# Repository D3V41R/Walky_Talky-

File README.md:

**Walky-Talky**

Walky-Talky is a custom **STM32-based** digital voice communication system built for long-range, low-bandwidth voice transmission over LoRa RF.

The project combines embedded firmware development, custom PCB design in KiCad, digital signal processing, and wireless communication into a fully self-contained handheld device.

Voice audio is captured using an INMP441 I2S microphone, compressed in real time using the Codec2 low-bitrate voice codec, and transmitted through a RYLR998 LoRa module operating at 915 MHz. On the receiving side, audio is decoded and played back through a 12-bit DAC and PAM8403 speaker amplifier.

To support continuous real-time streaming, STM32 DMA is used throughout both the audio and RF pipelines, minimizing CPU overhead while maintaining low-latency operation.

The hardware was designed entirely from scratch in KiCad and includes custom analog audio circuitry, rotary encoder channel selection, power regulation, and RF interfacing on a fully custom PCB.

**Features**
-Real-time digital voice communication over LoRa
-Codec2 low-bitrate voice compression
-STM32 DMA-driven audio streaming
-INMP441 I2S microphone input
-12-bit DAC audio playback
-PAM8403 speaker amplifier output
-Rotary encoder channel selection
-Fully custom KiCad PCB design
-Embedded real-time firmware architecture

**System Diagram**

**Hardware Overview**

Schematic:

PCB Renderings: 

**Technologies Used**
STM32
KiCad
LoRa / RYLR998
Codec2
I2S Audio
DMA Streaming
Embedded C
Digital Signal Processing
Custom PCB Design

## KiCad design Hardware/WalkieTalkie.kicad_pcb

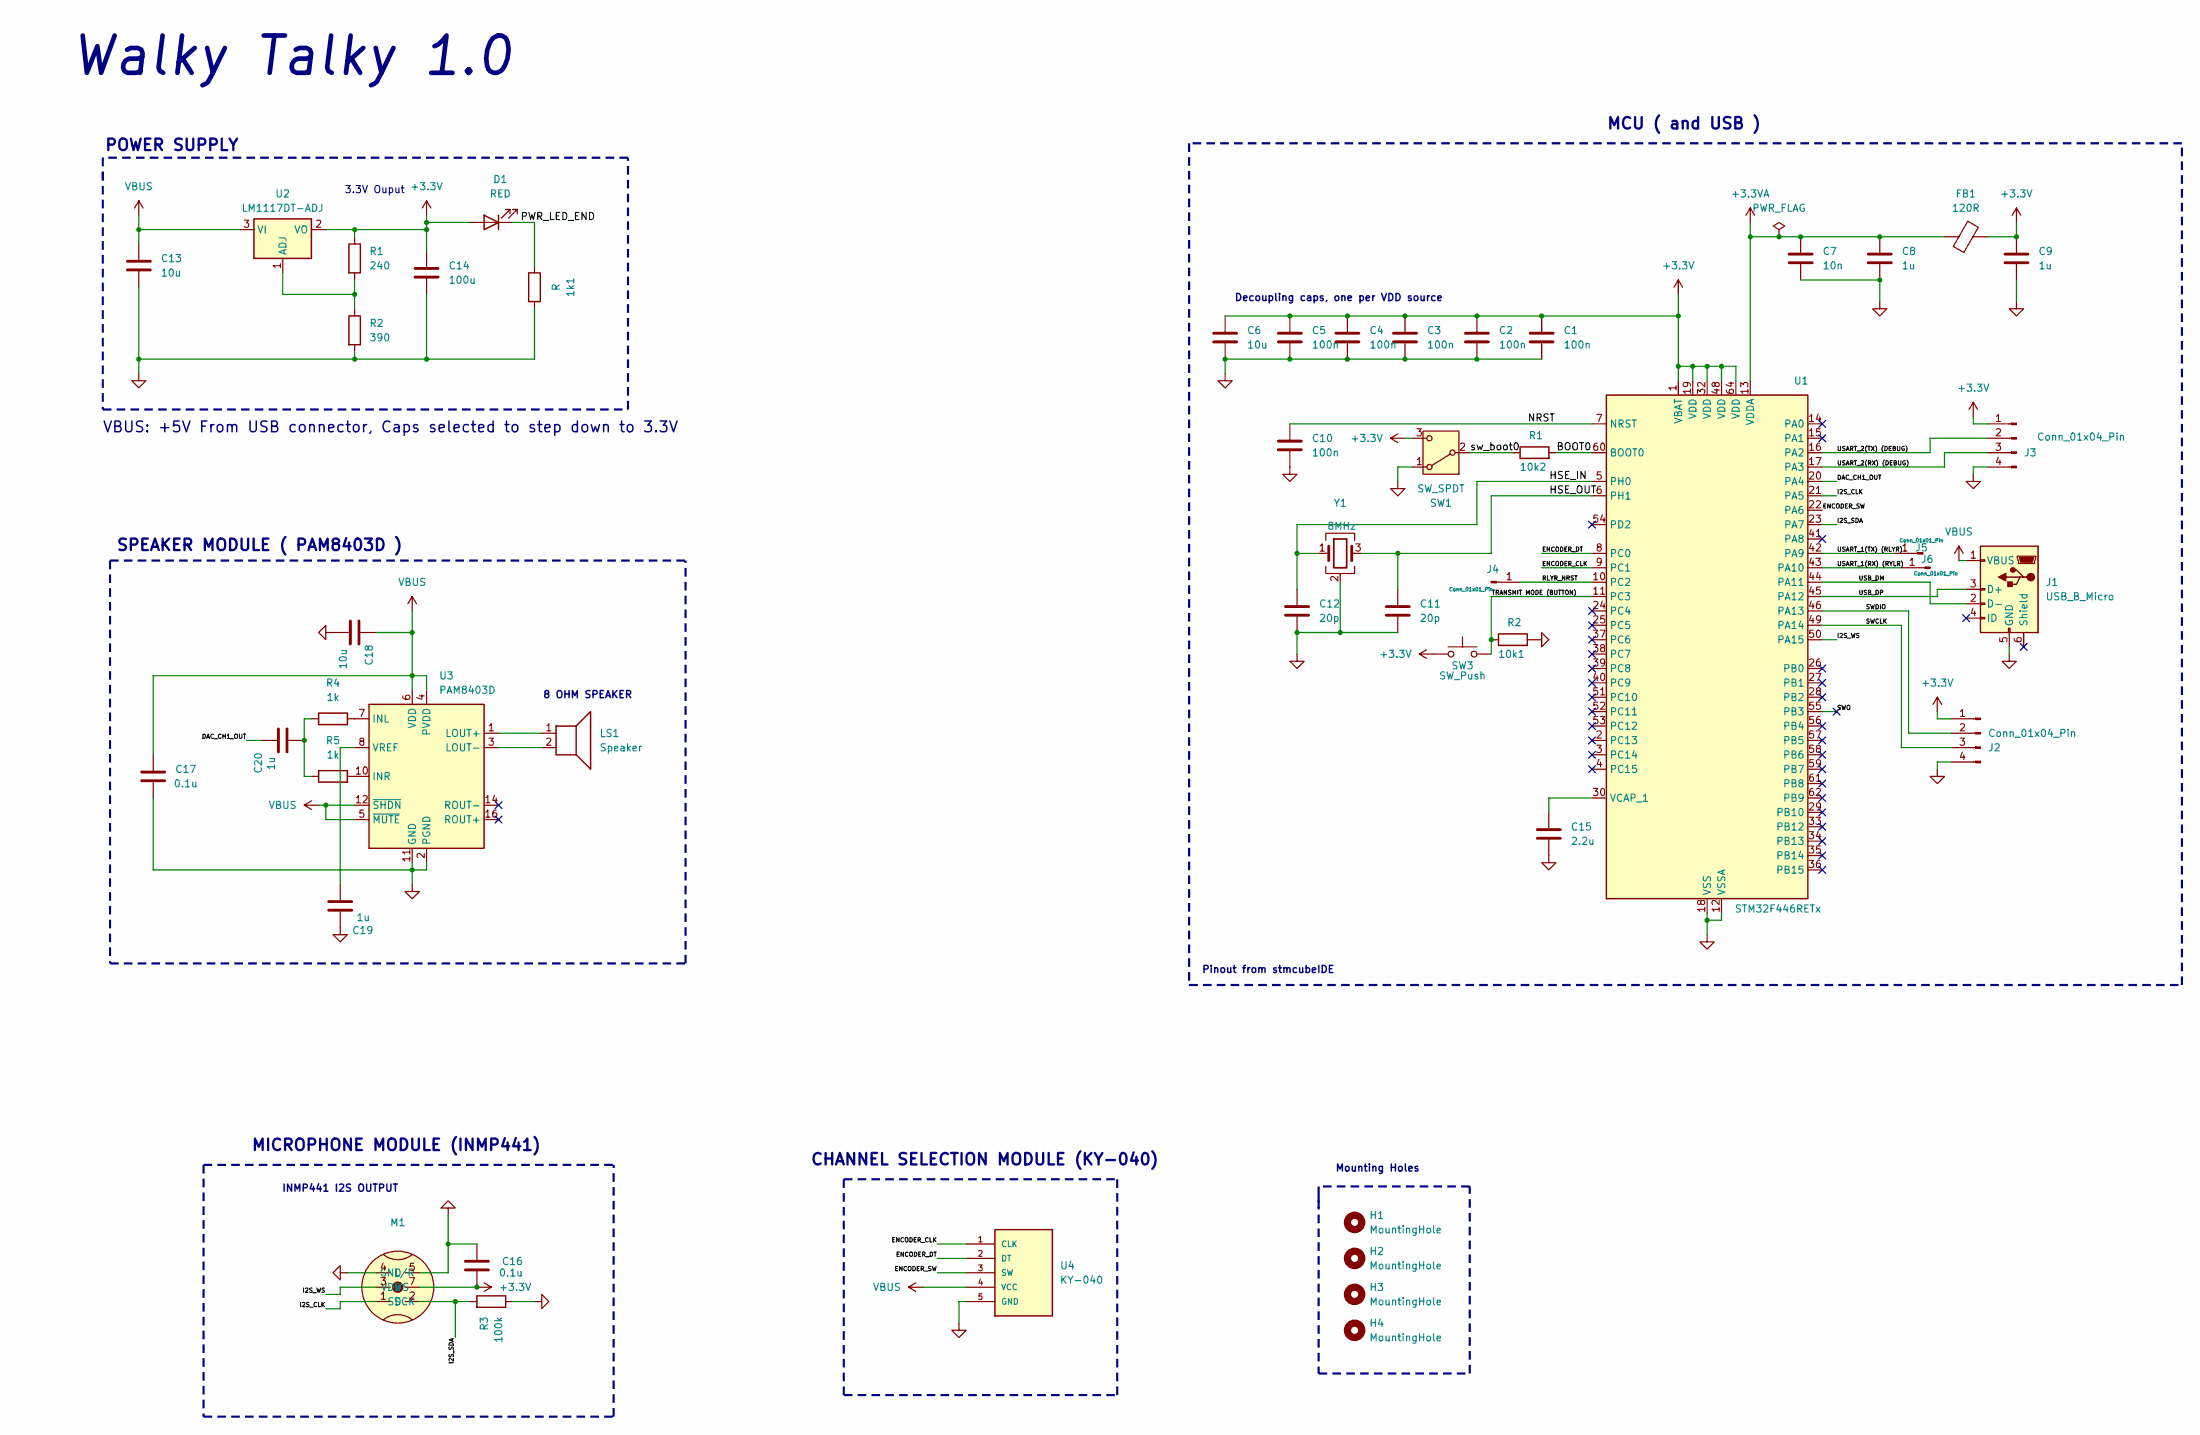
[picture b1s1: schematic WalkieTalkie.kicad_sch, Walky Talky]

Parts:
1k1: R; R_0603_1608Metric
10k1: R2; R_0603_1608Metric
10k2: R1; R_0603_1608Metric
C1, C2, C3, C4, C5, C10: 100n; C_0603_1608Metric
C6, C13, C18: 10u; C_0603_1608Metric
C7: 10n; C_0603_1608Metric
C8, C9, C19, C20: 1u; C_0603_1608Metric
C11, C12: 20p; C_0603_1608Metric
C14: 100u; C_0603_1608Metric
C15: 2.2u; C_0603_1608Metric
C16, C17: 0.1u; C_0603_1608Metric
D1: RED; LED_0201_0603Metric
FB1: 120R; L_0603_1608Metric
H1, H2, H3, H4: MountingHole; MountingHole_2.2mm_M2
J1: USB_B_Micro; USB_Micro-B_Wuerth_629105150521
J2, J3: Conn_01x04_Pin; PinHeader_1x04_P2.54mm_Vertical
J4, J5, J6: Conn_01x01_Pin; PinSocket_1x01_P2.54mm_Horizontal
LS1: Speaker; PinHeader_1x02_P2.54mm_Vertical
M1: MIC_INMP441ACEZ-R7
R1: 240; R_0603_1608Metric
R2: 390; R_0603_1608Metric
R3: 100k; R_0603_1608Metric
R4, R5: 1k; R_0603_1608Metric
SW1: SW_SPDT; SW_SPDT_PCM12
SW3: SW_Push; SW_DIP_SPSTx01_Slide_6.7x4.1mm_W7.62mm_P2.54mm_LowProfile
U1: STM32F446RETx; LQFP-64_10x10mm_P0.5mm
U2: LM1117DT-ADJ; TO-252-3_TabPin2
U3: PAM8403D; SOIC-16_3.9x9.9mm_P1.27mm
U4: KY-040; PinHeader_1x05_P2.54mm_Vertical
Y1: 8MHz; Crystal_SMD_3225-4Pin_3.2x2.5mm

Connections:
+3.3V: C1.1, C2.1, C3.1, C4.1, C5.1, C6.1, C9.1, C14.1, C16.2, D1.2 (A), FB1.2, J2.1, J3.1, M1.7 (VDD), R1.1, SW1.3 (C), SW3.1, U1.1 (VBAT), U1.19 (VDD), U1.32 (VDD), U1.48 (VDD), U1.64 (VDD), U2.2 (VO)
+3.3VA: C7.1, C8.1, FB1.1, U1.13 (VDDA)
/BOOT0: 10k2.2, U1.60 (BOOT0)
/DAC_CH1_OUT: C20.2, U1.20 (PA4)
/ENCODER_CLK: U1.9 (PC1), U4.1 (CLK)
/ENCODER_DT: U1.8 (PC0), U4.2 (DT)
/ENCODER_SW: U1.22 (PA6), U4.3 (SW)
/HSE_IN: C12.1, U1.5 (PH0), Y1.1
/HSE_OUT: C11.1, U1.6 (PH1), Y1.3
/I2S_CLK: M1.1 (SCK), U1.21 (PA5)
/I2S_SDA: M1.2 (SD), R3.2, U1.23 (PA7)
/I2S_WS: M1.3 (WS), U1.50 (PA15)
/NRST: C10.1, U1.7 (NRST)
/PWR_LED_END: 1k1.1, D1.1 (K)
/RLYR_NRST: J4.1, U1.10 (PC2)
/SWCLK: J2.3, U1.49 (PA14)
/SWDIO: J2.2, U1.46 (PA13)
/SWO: U1.55 (PB3)
/TRANSMIT MODE (BUTTON): 10k1.1, SW3.2, U1.11 (PC3)
/USART_1(RX) (RYLR): J6.1, U1.43 (PA10)
/USART_1(TX) (RLYR): J5.1, U1.42 (PA9)
/USART_2(RX) (DEBUG): J3.3, U1.17 (PA3)
/USART_2(TX) (DEBUG): J3.2, U1.16 (PA2)
/USB_DM: J1.2 (D-), U1.44 (PA11)
/USB_DP: J1.3 (D+), U1.45 (PA12)
/sw_boot0: 10k2.1, SW1.2 (B)
GND: 1k1.2, 10k1.2, C1.2, C2.2, C3.2, C4.2, C5.2, C6.2, C7.2, C8.2, C9.2, C10.2, C11.2, C12.2, C13.2, C14.2, C15.2, C16.1, C17.2, C18.2, C19.2, J1.5 (GND), J2.4, J3.4, M1.4 (L/R), M1.5 (GND), R2.2, R3.1, SW1.1 (A), U1.12 (VSSA), U1.18 (VSS), U1.31 (VSS), U1.47 (VSS), U1.63 (VSS), U3.2 (PGND), U3.11 (GND), U3.15 (PGND), U4.5 (GND), Y1.2 (G), Y1.4 (G)
unnamed: C20.1, R4.1, R5.1
unnamed: C15.1, U1.30 (VCAP_1)
unnamed: R1.2, R2.1, U2.1 (ADJ)
unnamed: R4.2, U3.7 (INL)
unnamed: R5.2, U3.10 (INR)
unnamed: LS1.1, U3.1 (LOUT+)
unnamed: LS1.2, U3.3 (LOUT-)
unnamed: C19.1, U3.8 (VREF)
VBUS: C13.1, C17.1, C18.1, J1.1 (VBUS), U2.3 (VI), U3.4 (PVDD), U3.5 (~MUTE), U3.6 (VDD), U3.12 (~SHDN), U3.13 (PVDD), U4.4 (VCC)

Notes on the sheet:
INMP441 I2S OUTPUT
CHANNEL SELECTION MODULE (KY-040)
VBUS: +5V From USB connector, Caps selected to step down to 3.3V
Pinout from stmcubeIDE
Walky Talky 1.0
MCU ( and USB )
3.3V Ouput
8 OHM SPEAKER
POWER SUPPLY
Decoupling caps, one per VDD source
MICROPHONE MODULE (INMP441)
Mounting Holes
SPEAKER MODULE ( PAM8403D )

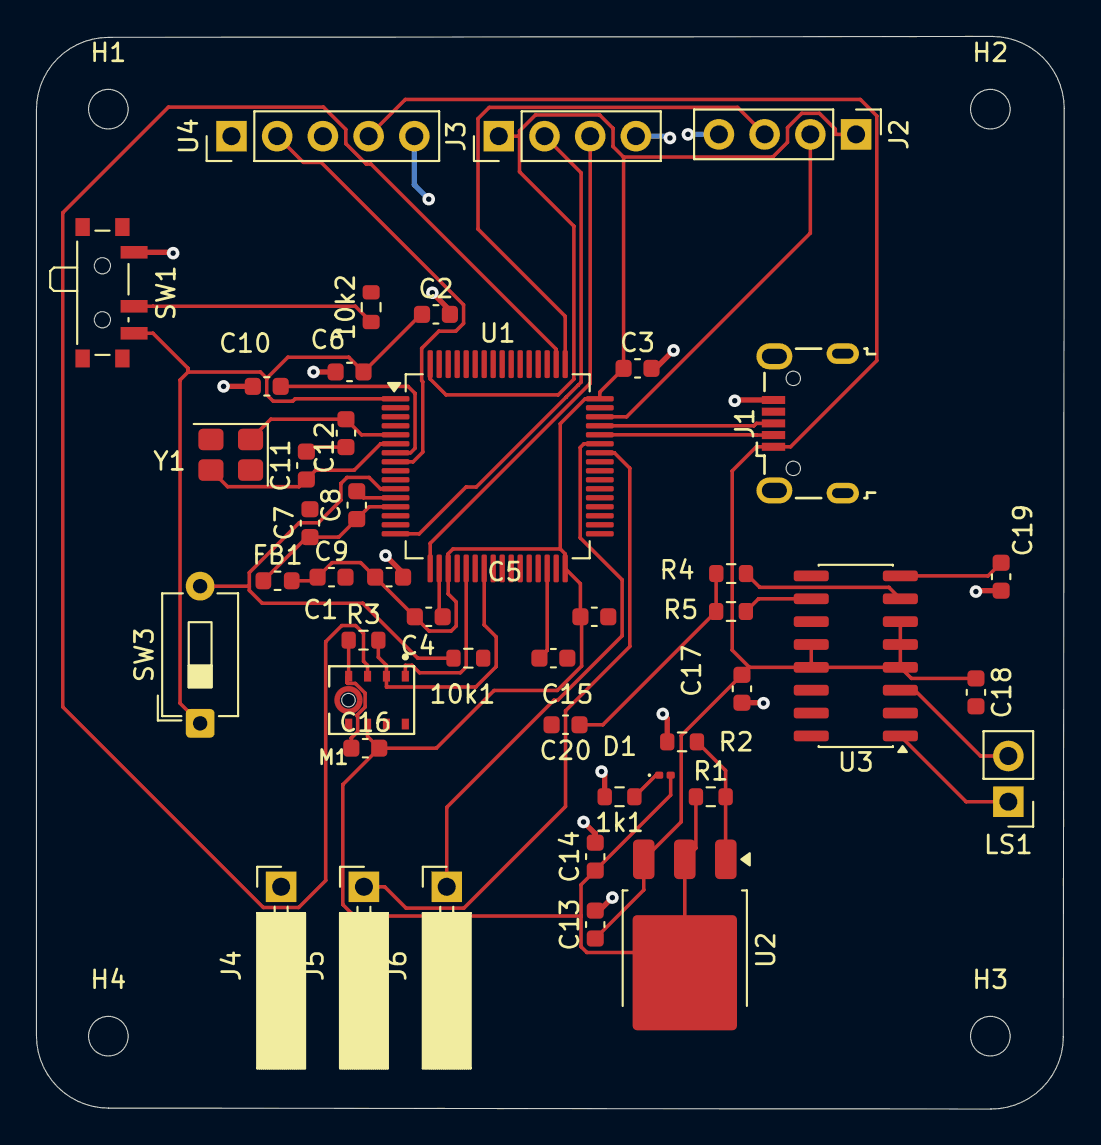
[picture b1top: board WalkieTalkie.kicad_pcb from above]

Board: 2 copper layers, 57.1 x 59.6 mm, 49 parts (0 on the bottom side), 35 nets.

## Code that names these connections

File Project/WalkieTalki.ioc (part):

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Mcu.Name=STM32F446R(C-E)Tx
Mcu.Package=LQFP64
Mcu.UserName=STM32F446RETx
PA10.Mode=Asynchronous
PA10.Signal=USART1_RX
PA11.Mode=Device_Only
PA11.Signal=USB_OTG_FS_DM
PA12.Mode=Device_Only
PA12.Signal=USB_OTG_FS_DP
PA13.GPIOParameters=GPIO_Label
PA13.GPIO_Label=TMS
PA13.Mode=Serial_Wire
PA13.Signal=SYS_JTMS-SWDIO
PA14.GPIOParameters=GPIO_Label
PA14.GPIO_Label=TCK
PA14.Mode=Serial_Wire
PA14.Signal=SYS_JTCK-SWCLK
PA15.Mode=Half_Duplex_Master
PA15.Signal=I2S1_WS
PA2.Mode=Asynchronous
PA2.Signal=USART2_TX
PA3.Mode=Asynchronous
PA3.Signal=USART2_RX
PA4.GPIOParameters=GPIO_Label
PA4.GPIO_Label=DAC_OUTPUT
PA4.Signal=SharedAnalog_PA4
PA5.Mode=Half_Duplex_Master
PA5.Signal=I2S1_CK
PA6.GPIOParameters=GPIO_Label
PA6.GPIO_Label=ENCODER_SW
PA6.Signal=GPIO_Input
PA7.Mode=Half_Duplex_Master
PA7.Signal=I2S1_SD
PA9.Mode=Asynchronous
PA9.Signal=USART1_TX
PB3.GPIOParameters=GPIO_Label
PB3.GPIO_Label=SWO
PB3.Signal=SYS_JTDO-SWO
PC0.GPIOParameters=GPIO_PuPd,GPIO_Label
PC0.GPIO_Label=Encoder_DT
PC0.GPIO_PuPd=GPIO_PULLUP
PC0.Signal=GPIO_Input
PC1.GPIOParameters=GPIO_PuPd,GPIO_Label
PC1.GPIO_Label=Encoder_CLK
PC1.GPIO_PuPd=GPIO_PULLUP
PC1.Signal=GPIO_Input
PC14-OSC32_IN.Mode=LSE-External-Oscillator
PC14-OSC32_IN.Signal=RCC_OSC32_IN
PC15-OSC32_OUT.Mode=LSE-External-Oscillator
PC15-OSC32_OUT.Signal=RCC_OSC32_OUT
PC2.GPIOParameters=GPIO_Label
PC2.GPIO_Label=RLYR_NRST
PC2.Signal=GPIO_Output
PC3.GPIOParameters=GPIO_Label
PC3.GPIO_Label=TRANSMIT MODE (BUTTON)
PC3.Signal=GPIO_Output
PH0-OSC_IN.Mode=HSE-External-Oscillator
PH0-OSC_IN.Signal=RCC_OSC_IN
PH1-OSC_OUT.Mode=HSE-External-Oscillator
PH1-OSC_OUT.Signal=RCC_OSC_OUT
RCC.HSE_VALUE=8000000
RCC.SYSCLKFreq_VALUE=72000000
RCC.SYSCLKSource=RCC_SYSCLKSOURCE_PLLCLK
board=NUCLEO-F446RE
boardIOC=true

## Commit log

2026-05-21 Add README for Walky-Talky project
    Added project overview and technical details for Walky-Talky.
2026-05-22 Revise README.md for improved project overview
    Updated project description for clarity and detail.
2026-05-22 Added Hardware Design Files
2026-05-22 Rename WalkieTalkie.kicad_pcb to Hardware/WalkieTalkie.kicad_pcb
2026-05-22 Rename WalkieTalkie.kicad_pro to Hardware /WalkieTalkie.kicad_pro
2026-05-26 Added project files
2026-05-27 Implemented Rlyrr Driver, Completed Microphone Driver.
